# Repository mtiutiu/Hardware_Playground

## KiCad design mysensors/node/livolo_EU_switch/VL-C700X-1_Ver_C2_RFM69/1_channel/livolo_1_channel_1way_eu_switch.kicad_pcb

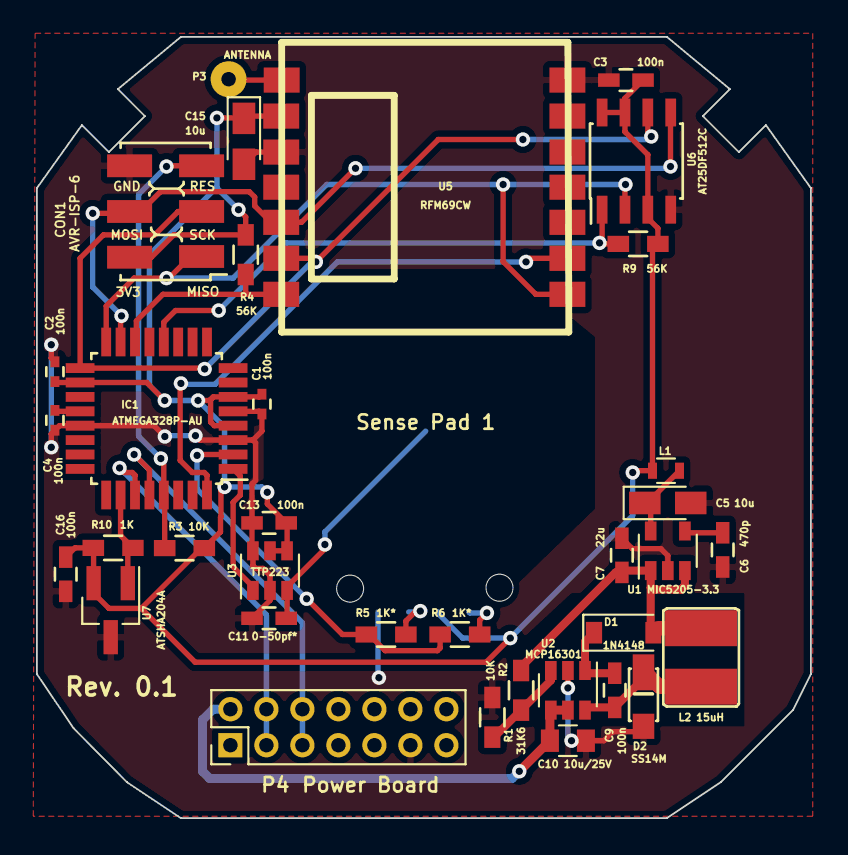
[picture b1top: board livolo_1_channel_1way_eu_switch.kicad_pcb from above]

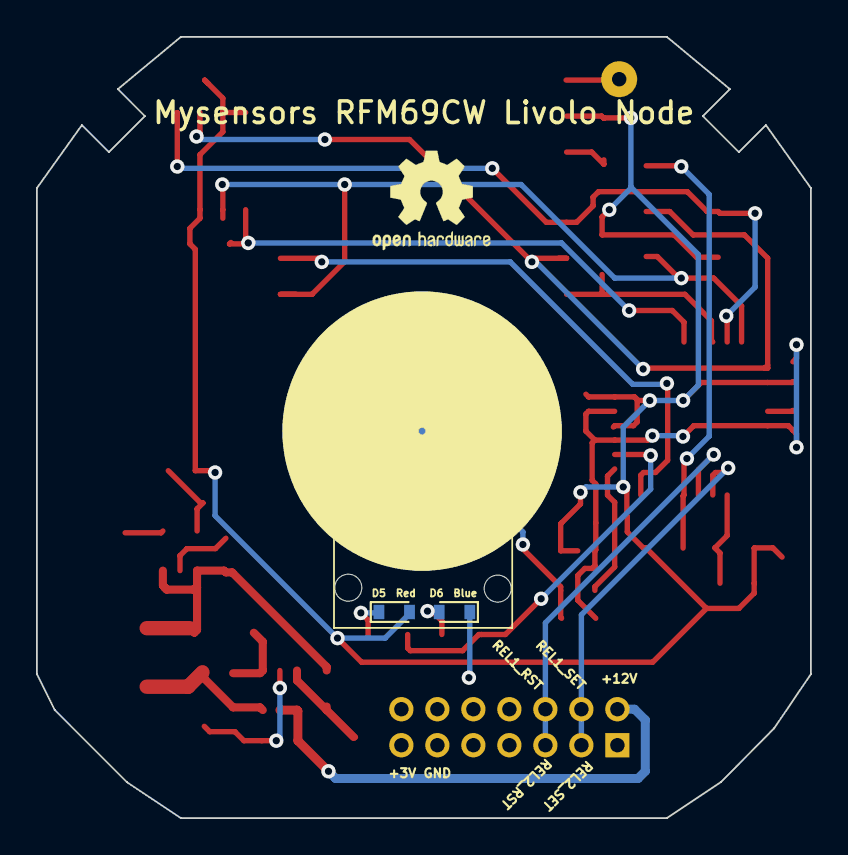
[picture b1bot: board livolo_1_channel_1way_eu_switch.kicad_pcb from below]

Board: 2 copper layers, 43.0 x 43.4 mm, 38 parts (2 on the bottom side), 26 nets.

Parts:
C1, C2, C4: 100n; C_0402
C3, C9, C13, C16: 100n; C_0603_HandSoldering
C5, C15: 10u; CP_Tantalum_Case-R_EIA-2012-12_Wave
C6: 470p; C_0603_HandSoldering
C7: 22u; C_0603_HandSoldering
C10: 10u/25V; C_0805
C11: 0-50pf*; C_0603_HandSoldering
CON1: AVR-ISP-6; AVR_ISP_SMT_Small_02x03
D1: 1N4148; SOD-123
D2: SS14M
D5: Red; D_0603
D6: Blue; D_0603
IC1: ATMEGA328P-AU; TQFP-32_7x7mm_Pitch0.8mm
L1: BLM18HE152SN1D; R_0603
L2: 15uH; VLCF4020T-150MR68
P1: Sense Pad 1; touch_pad_16mm
P3: ANTENNA; SolderWirePad_single_0-8mmDrill
P4: Power Board; Pin_Header_Straight_2x07_Pitch2.00mm
R1: 31K6; R_0603_HandSoldering
R2, R3: 10K; R_0603_HandSoldering
R4, R9: 56K; R_0603_HandSoldering
R5, R6: 1K*; R_0603_HandSoldering
R10: 1K; R_0603_HandSoldering
U1: MIC5205-3.3; SOT-23-5
U2: MCP16301; SOT-23-6
U3: TTP223; SOT-23-6
U5: RFM69CW
U6: AT25DF512C; SOIC-8_3.9x4.9mm_Pitch1.27mm
U7: ATSHA204A; SOT-23_Handsoldering

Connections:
+3V3: C1.1, C2.2, C3.2, C13.1, C15.1, C16.2, CON1.2, D5.2, IC1.4, IC1.6, IC1.18, L1.1, R3.1, R4.2, R9.1, R10.1, U3.4, U3.5, U5.2, U6.3, U6.7, U6.8, U7.2
/12Vcc: C10.1, P4.2, U2.4, U2.5
/ATSHA204A: IC1.26, R10.2, U7.1
/FLASH_SS: IC1.12, R9.2, U6.1
/INT: IC1.32, U5.9
/MISO: CON1.1, IC1.16, U5.8, U6.2
/MOSI: CON1.4, IC1.15, U5.5, U6.5
/RADIO_SS: IC1.14, R4.1, U5.7
/RESET: CON1.5, IC1.29, R3.2
/Relay1_Reset: IC1.28, P4.5, P4.6
/Relay1_Set: IC1.27, P4.3, P4.4
/S1_LEDs: IC1.2, R5.2, R6.2
/SCK: CON1.3, IC1.17, U5.6, U6.6
/TS1: IC1.1, U3.1
GND: C1.2, C2.1, C3.1, C4.1, C5.2, C6.2, C7.2, C10.2, C11.2, C13.2, C15.2, C16.1, CON1.6, D2.2, D6.1, IC1.3, IC1.5, IC1.21, P4.11, R2.1, U1.2, U2.2, U3.2, U3.6, U5.3, U5.14, U6.4, U7.3
unnamed: C4.2, IC1.20
unnamed: C5.1, L1.2, U1.5
unnamed: C6.1, U1.4
unnamed: C7.1, D1.2, L2.1, R1.2, U1.1, U1.3
unnamed: C9.1, D1.1, U2.1
unnamed: C9.2, D2.1, L2.2, U2.6
unnamed: C11.1, P1.1, U3.3
unnamed: D5.1, R6.1
unnamed: D6.2, R5.1
unnamed: P3.1, U5.1
unnamed: R1.1, R2.2, U2.3

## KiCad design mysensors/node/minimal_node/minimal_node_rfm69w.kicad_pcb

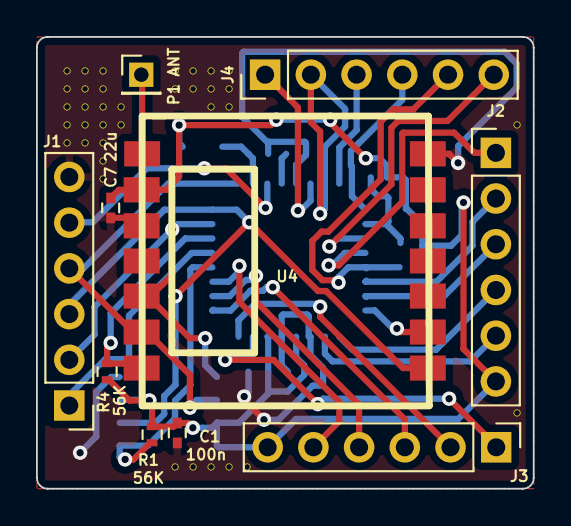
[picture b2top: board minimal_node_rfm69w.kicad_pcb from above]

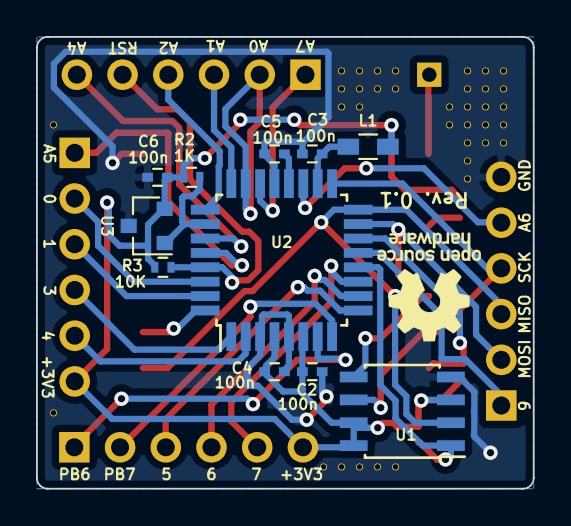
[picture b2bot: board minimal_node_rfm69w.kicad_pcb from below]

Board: 2 copper layers, 27.6 x 25.1 mm, 57 parts (11 on the bottom side), 30 nets.

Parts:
C1, C2, C3, C4, C5, C6: 100n; C_0402
C7: 22u; C_0402
J1, J2, J3, J4: CONN_01X06; Pin_Header_Straight_1x06_Pitch2.54mm
L1: BLM18HE152; R_0603_HandSoldering
P1: ANT; Pin_Header_Straight_1x01_Pitch2.00mm
R1, R4: 56K; R_0402
R2: 1K; R_0402
R3: 10K; R_0402
U1: AT25DF512C; SOIC-8_3.9x4.9mm_Pitch1.27mm
U2: ATMEGA328P-AU; TQFP-32_7x7mm_Pitch0.8mm
U3: ATSHA204A; SOT-23
U4: RFM69CW
V8_3, V8_4, V8_5, V8_6, V8_7, V9_3, V9_4, V9_5, V9_6, V9_7, V10_3, V10_4, V10_5, V10_6, V10_7, V10_8, V10_9, V11_5, V11_6, V14_3, V14_4, V14_25, V15_3, V15_4, V15_25, V16_3, V16_4, V16_5, V16_25, V17_3, V17_4, V17_5, V17_25, V18_25, V33_6, V33_22: AUTO_VIA; VIA_MATRIX

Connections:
+3V3: C1.2, C2.1, C4.2, C6.1, C7.1, J2.6, J3.6, L1.2, R1.2, R2.2, R3.1, R4.2, U1.3, U1.7, U1.8, U2.4, U2.6, U3.2, U4.2
/7: J3.1, U2.7
/8: J3.2, U2.8
/19: J1.5, U2.19
/22: J4.1, U2.22
/ATSHA204A: R2.1, U2.26, U3.1
/MISO: J1.3, U1.2, U2.16, U4.8
/MOSI: J1.2, U1.5, U2.15, U4.5
/RFM69W_INT: U2.32, U4.9
/RFM69W_SS: R4.1, U2.14, U4.7
/RST: J4.5, R3.2, U2.29
/SCK: J1.4, U1.6, U2.17, U4.6
/SPI_FLASH_SS: R1.1, U1.1, U2.12
GND: C1.1, C2.2, C3.1, C4.1, C5.1, C6.2, C7.2, J1.6, U1.4, U2.3, U2.5, U2.21, U3.3, U4.3, U4.14, V8_3.1, V8_4.1, V8_5.1, V8_6.1, V8_7.1, V9_3.1, V9_4.1, V9_5.1, V9_6.1, V9_7.1, V10_3.1, V10_4.1, V10_5.1, V10_6.1, V10_7.1, V10_8.1, V10_9.1, V11_5.1, V11_6.1, V14_3.1, V14_4.1, V14_25.1, V15_3.1, V15_4.1, V15_25.1, V16_3.1, V16_4.1, V16_5.1, V16_25.1, V17_3.1, V17_4.1, V17_5.1, V17_25.1, V18_25.1, V33_6.1, V33_22.1
unnamed: C3.2, L1.1, U2.18
unnamed: C5.2, U2.20
unnamed: J1.1, U2.13
unnamed: J2.1, U2.28
unnamed: J2.2, U2.30
unnamed: J2.3, U2.31
unnamed: J2.4, U2.1
unnamed: J2.5, U2.2
unnamed: J3.3, U2.9
unnamed: J3.4, U2.10
unnamed: J3.5, U2.11
unnamed: J4.2, U2.23
unnamed: J4.3, U2.24
unnamed: J4.4, U2.25
unnamed: J4.6, U2.27
unnamed: P1.1, U4.1

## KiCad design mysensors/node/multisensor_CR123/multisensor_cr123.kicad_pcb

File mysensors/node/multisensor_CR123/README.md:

## Mysensors RFM69W multisensor node(CR123)
More details here: https://www.openhardware.io/view/321/MySensors-RFM69W-multisensor-nodeCR123

##### 3D renderings of pcb

Top view | Bottom view
------------ | -------------
 | 

**Description:**

This is a Mysensors node using **RFM69W** radio module, **I2C based** temperature/humidity sensors(as external module) and **A3212** or equivalent hall effect sensors. 

**Key Features:**

 - **Si7021** temperature/humidity sensor(as a separate module bought from Aliexpress)
 - **A3212** hall efect sensor support
 - **DIP switch** for setting node ID statically
 - **MySensors** ready(**Atmega328p** + **RFM69W**)
 - **DC-DC boost** converter(**L6920** based) - can be bypassed if desired using the SMD jumpers on the board
 - **Small** board(**48 x 22mm**) using a **CR123** battery

**Work progress:**
 1. Test/verify the pcb board correctness(from both electrical and mechanical point of views) - **DONE**
 2. Produce the initial PCB's using some external PCB manufacturer - **DONE**
 3. Components assembly(soldering) - **DONE**
 4. Upload Mysensors temperature/humidity node sketch code - **DONE**
 5. Verify the real board with running code - **DONE**
 6. Code optimizations for low power operation - **DONE**
 7. Create project enclosure using a 3D printer - **DONE**

**Note:**

This module has been in production for about 2 months now and it's working stable. This is my first stable node created and I didn't provided any other features as signing support and SPI flash for OTA - so please bear this in mind. This is the final version of it and I won't invest any time/money or other resources to upgrade it. The project is open hardware anyway so anyone can do that if he/she wants.

**Credits:**
  
  All credits go to **MySensors** team for the great work and to the opensource community

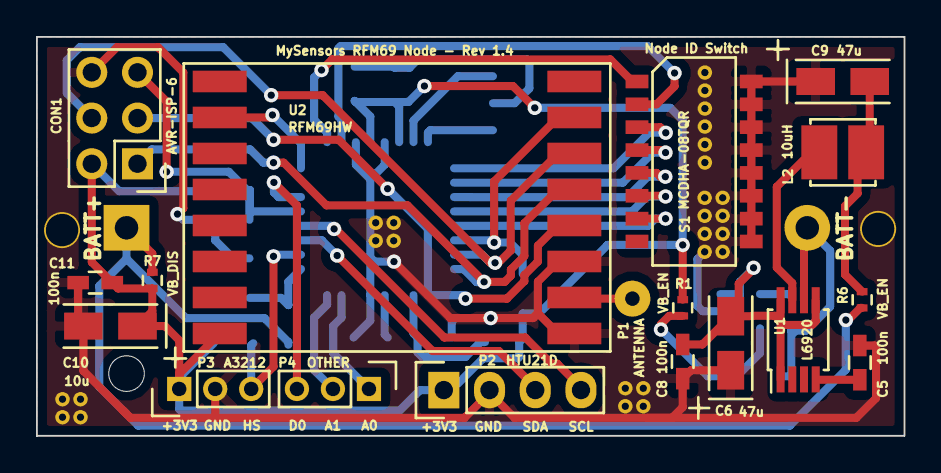
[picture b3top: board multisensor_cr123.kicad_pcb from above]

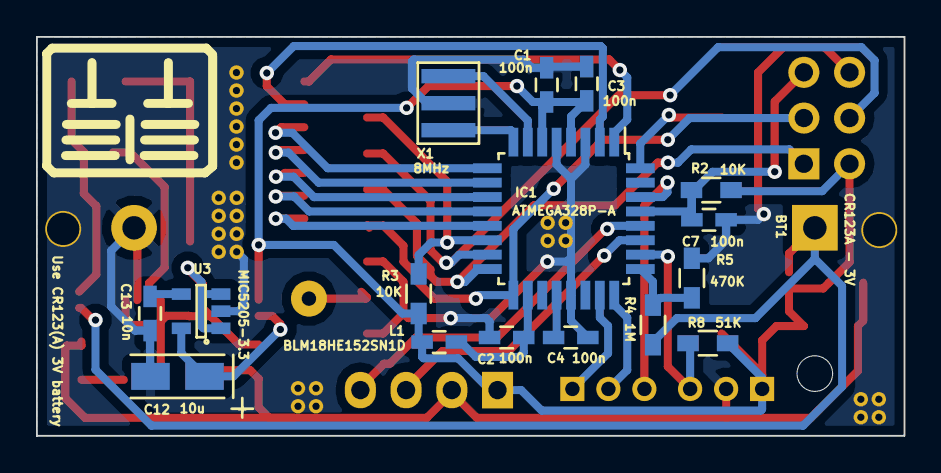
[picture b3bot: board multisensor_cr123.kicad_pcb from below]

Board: 2 copper layers, 48.2 x 22.2 mm, 35 parts (17 on the bottom side), 34 nets.

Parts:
BT1: CR123A - 3V; CR123_holder
C1, C2, C3, C4, C5, C7, C8, C11: 100n; C_0603_HandSoldering
C6, C9: 47u; TantalC_SizeA_EIA-3216_Wave
C10, C12: 10u; TantalC_SizeA_EIA-3216_Wave
C13: 10n; C_0603_HandSoldering
CON1: AVR-ISP-6; Pin_Header_Straight_2x03
IC1: ATMEGA328P-A; TQFP-32_7x7mm_Pitch0.8mm
L1: BLM18HE152SN1D; C_0603_HandSoldering
L2: 10uH; DLJ-3015
P1: ANTENNA; SolderWirePad_single_0-8mmDrill
P2: HTU21D; Pin_Header_Straight_1x04
P3: A3212; Pin_Header_Straight_1x03_Pitch2.00mm
P4: OTHER; Pin_Header_Straight_1x03_Pitch2.00mm
R1, R6: VB_EN; R_0402
R2, R3: 10K; R_0603_HandSoldering
R4: 1M; R_0603_HandSoldering
R5: 470K; R_0603_HandSoldering
R7: VB_DIS; R_0402
R8: 51K; R_0603_HandSoldering
S1: MCDHA-08TQR; DIPSWITCH_SMD_1.27-16
U1: L6920; MSOP-8_3x3mm_Pitch0.65mm
U2: RFM69HW; RFM69HW_SMD_Handsoldering
U3: MIC5205-3.3; SOT-23-5
X1: 8MHz; ZTTCR-3

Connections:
+3V3: C1.1, C3.2, C10.1, C11.1, CON1.2, IC1.4, IC1.6, L1.1, P2.1, P3.1, R1.2, R2.1, R3.2, R7.1, R8.1, U2.8
/A0: IC1.23, P4.1
/A1: IC1.24, P4.2
/C0: IC1.1, S1.1
/C1: IC1.2, S1.2
/C2: IC1.9, S1.3
/C3: IC1.10, S1.4
/C4: IC1.11, S1.5
/C5: IC1.12, S1.6
/C6: IC1.13, S1.7
/D0: IC1.30, P4.3
/HALL_SENSOR: IC1.26, P3.3, R8.2
/INT: IC1.32, U2.2
/MISO: CON1.1, IC1.16, U2.13
/MOSI: CON1.4, IC1.15, U2.14
/RESET: C7.2, CON1.5, IC1.29, R2.2
/SCK: CON1.3, IC1.17, U2.12
/SCL: IC1.28, P2.4
/SDA: IC1.27, P2.3
/SS: IC1.14, R3.1, U2.15
/V_BATT: IC1.25, R4.1, R5.2
/V_BOOST_IN: C9.2, L2.2, R6.2
GND: BT1.2, C1.2, C2.1, C3.1, C4.1, C5.2, C6.1, C7.1, C8.2, C9.1, C10.2, C11.2, C12.2, C13.2, CON1.6, IC1.3, IC1.5, IC1.21, P2.2, P3.2, R5.1, S1.9, S1.10, S1.11, S1.12, S1.13, S1.14, S1.15, S1.16, U1.6, U2.9, U2.11, U3.2, X1.3
unnamed: BT1.1, R4.2, R6.1, R7.2
unnamed: C2.2, IC1.18, L1.2
unnamed: C4.2, IC1.20
unnamed: C5.1, U1.4
unnamed: C6.2, C8.1, U1.1, U1.5, U1.8, U3.1, U3.3
unnamed: C12.1, R1.1, U3.5
unnamed: C13.1, U3.4
unnamed: IC1.7, X1.2
unnamed: IC1.8, X1.1
unnamed: L2.1, U1.7
unnamed: P1.1, U2.10

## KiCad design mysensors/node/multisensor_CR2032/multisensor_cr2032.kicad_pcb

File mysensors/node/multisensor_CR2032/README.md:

## Mysensors RFM69W multisensor node(CR2032)
More details here: https://www.openhardware.io/view/320/MySensors-RFM69W-multisensor-nodeCR2032

##### 3D renderings of pcb

Top view | Bottom view
------------ | -------------
 | 

**Description:**

This is a Mysensors node using **RFM69W** radio module, **Si7021** temperature/humidity sensor and **MAX44009** ambient light sensor. 

**Key Features:**

 - **Si7021** temperature/humidity sensor
 - **MAX44009** ambient light sensor
 - **ATSHA204A** for signing
 - **AT25DF512C-SSHN-B** SPI flash module for OTA
 - **MySensors** ready(**Atmega328p** + **RFM69W**)
 - **DC-DC boost** converter(**NCP1402** based) - can be bypassed using the on board jumpers
 - **Small** board(**36mm diameter**) using a **CR2032** coin cell

**Work progress:**
 1. Test/verify the pcb board correctness(from both electrical and mechanical point of views) - **TO DO**
 2. Produce the initial PCB's using some external PCB manufacturer
 3. Components assembly(soldering)
 4. Upload Mysensors temperature/humidity node sketch code
 5. Verify the real board with running code
 6. Code optimizations for low power operation
 7. Create project enclosure using a 3D printer

**Note: Work in progress(schematic/pcb will change).**

**HW Revisions:**
 - 0.1 - initial design
 - 0.2 - added option to bypass step-up converter using jumpers
 - 0.3 - added MAX44009 ambient light sensor
 - 0.4 - added A3212 hall sensor

**Kindly notice:**

The only thing I ask if using this project is to at least mention my name and if I don't ask too much you can also support my effort using the below button. Thanks for buying me a beer :).

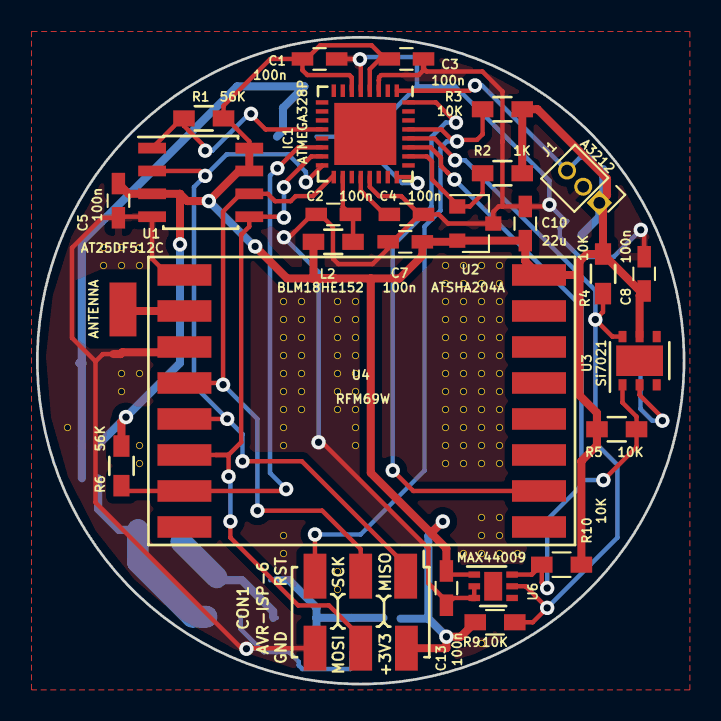
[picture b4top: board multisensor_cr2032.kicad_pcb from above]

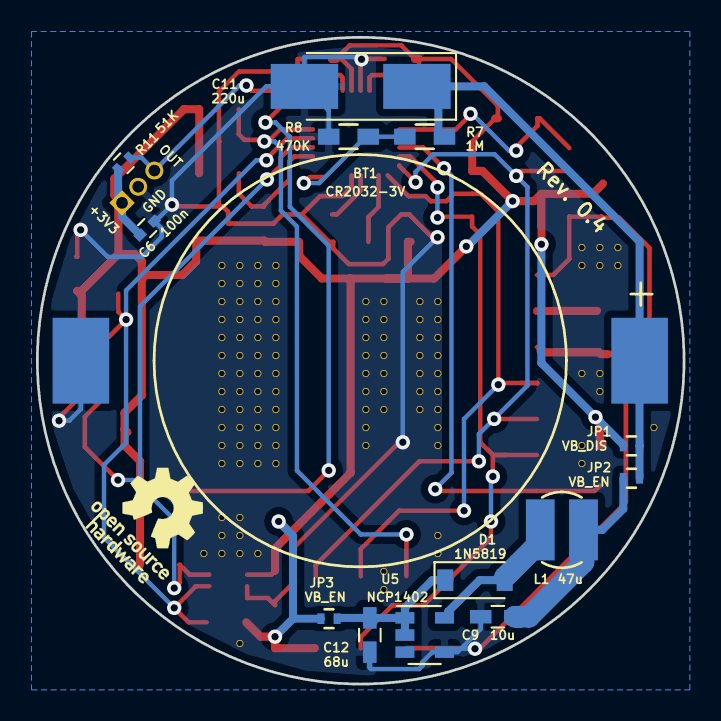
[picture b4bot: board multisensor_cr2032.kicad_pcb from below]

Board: 2 copper layers, 35.9 x 35.9 mm, 146 parts (14 on the bottom side), 21 nets.

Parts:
BT1: CR2032-3V; CR2032_BATT-HOLDER_SMT_H2
C1, C2, C3, C4, C5, C7, C8, C13: 100n; C_0603_HandSoldering
C6: 100n; C_0402
C9: 10u; C_0603_HandSoldering
C10: 22u; C_0603_HandSoldering
C11: 220u; CP_Tantalum_Case-C_EIA-6032-28_Hand
C12: 68u; C_0603_HandSoldering
CON1: AVR-ISP-6; AVR_ISP_SMT_Small_02x03
D1: 1N5819; D_SOD-123
IC1: ATMEGA328P; QFN-32-1EP_5x5mm_Pitch0.5mm
J1: A3212; Pin_Header_Straight_1x03_Pitch1.27mm
JP1, JP3: VB_EN; R_0402
JP2: VB_DIS; R_0402
L1: 47u; SDR0302
L2: BLM18HE152; R_0603_HandSoldering
P1: ANTENNA; 1pin_smd_2mm
R1, R6: 56K; R_0603_HandSoldering
R2: 1K; R_0603_HandSoldering
R3, R4, R5, R9, R10: 10K; R_0603_HandSoldering
R7: 1M; R_0603_HandSoldering
R8: 470K; R_0603_HandSoldering
R11: 51K; R_0402
U1: AT25DF512C; SOIC-8_3.9x4.9mm_Pitch1.27mm
U2: ATSHA204A; SOT-23
U3: Si7021; DFN-6-1EP_3x3mm_Pitch0.95mm
U4: RFM69W; RFM69HW_SMD_Handsoldering
U5: NCP1402; SOT-23-5
U6: MAX44009; DFN-6-1EP_2x2mm_Pitch0.65mm
V2_22, V4_12, V4_13, V5_12, V5_13, V5_19, V5_20, V6_12, V6_13, V6_19, V6_23, V6_24, V14_15, V14_16, V14_17, V14_18, V14_19, V14_20, V14_21, V14_22, V14_23, V14_28, V14_29, V15_15, V15_16, V15_17, V15_18, V15_19, V15_20, V15_21, V17_15, V17_16, V17_17, V17_18, V17_19, V17_20, V17_21, V17_30, V17_31, V18_15, V18_16, V18_17, V18_18, V18_19, V18_20, V18_21, V18_22, V18_23, V23_13, V23_14, V23_15, V23_16, V23_17, V23_18, V23_19, V23_20, V23_21, V23_22, V23_23, V23_24, V24_13, V24_14, V24_15, V24_16, V24_17, V24_18, V24_19, V24_20, V24_21, V24_22, V24_23, V24_24, V24_29, V25_13, V25_14, V25_15, V25_16, V25_17, V25_18, V25_19, V25_20, V25_21, V25_22, V25_23, V25_24, V25_27, V25_28, V25_29, V25_34, V26_13, V26_14, V26_15, V26_16, V26_17, V26_18, V26_19, V26_20, V26_21, V26_22, V26_23, V26_24, V26_27, V26_28, V26_29, V27_29: AUTO_VIA; VIA_MATRIX

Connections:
+3V3: C1.1, C3.2, C5.2, C6.2, C7.1, C8.1, C10.1, C13.1, CON1.2, IC1.4, IC1.6, J1.1, JP2.2, JP3.2, L2.2, R1.2, R2.2, R3.1, R4.2, R5.2, R6.2, R9.2, R10.2, R11.1, U1.3, U1.7, U1.8, U2.2, U3.5, U4.8, U6.1
/A3212: IC1.1, J1.3, R11.2
/ATSHA204A: IC1.26, R2.1, U2.1
/MISO: CON1.1, IC1.16, U1.2, U4.13
/MOSI: CON1.4, IC1.15, U1.5, U4.14
/RFM69W_INT: IC1.32, U4.2
/RFM69W_SS: IC1.14, R6.1, U4.15
/RST: CON1.5, IC1.29, R3.2
/SCK: CON1.3, IC1.17, U1.6, U4.12
/SCL: IC1.28, R4.1, R9.1, U3.6, U6.5
/SDA: IC1.27, R5.1, R10.1, U3.1, U6.6
/SPI_FLASH_SS: IC1.12, R1.1, U1.1
/VB_IN: C9.2, JP1.1, L1.1
/V_BATT_MON: IC1.24, R7.1, R8.2
GND: BT1.2, C1.2, C2.1, C3.1, C4.1, C5.1, C6.1, C7.2, C8.2, C9.1, C10.2, C11.2, C12.1, C13.2, CON1.6, IC1.3, IC1.5, IC1.21, J1.2, R8.1, U1.4, U2.3, U3.2, U4.9, U4.11, U5.4, U6.2, U6.3, V2_22.1, V4_12.1, V4_13.1, V5_12.1, V5_13.1, V5_19.1, V5_20.1, V6_12.1, V6_13.1, V6_19.1, V6_23.1, V6_24.1, V14_15.1, V14_16.1, V14_17.1, V14_18.1, V14_19.1, V14_20.1, V14_21.1, V14_22.1, V14_23.1, V14_28.1, V14_29.1, V15_15.1, V15_16.1, V15_17.1, V15_18.1, V15_19.1, V15_20.1, V15_21.1, V17_15.1, V17_16.1, V17_17.1, V17_18.1, V17_19.1, V17_20.1, V17_21.1, V17_30.1, V17_31.1, V18_15.1, V18_16.1, V18_17.1, V18_18.1, V18_19.1, V18_20.1, V18_21.1, V18_22.1, V18_23.1, V23_13.1, V23_14.1, V23_15.1, V23_16.1, V23_17.1, V23_18.1, V23_19.1, V23_20.1, V23_21.1, V23_22.1, V23_23.1, V23_24.1, V24_13.1, V24_14.1, V24_15.1, V24_16.1, V24_17.1, V24_18.1, V24_19.1, V24_20.1, V24_21.1, V24_22.1, V24_23.1, V24_24.1, V24_29.1, V25_13.1, V25_14.1, V25_15.1, V25_16.1, V25_17.1, V25_18.1, V25_19.1, V25_20.1, V25_21.1, V25_22.1, V25_23.1, V25_24.1, V25_27.1, V25_28.1, V25_29.1, V25_34.1, V26_13.1, V26_14.1, V26_15.1, V26_16.1, V26_17.1, V26_18.1, V26_19.1, V26_20.1, V26_21.1, V26_22.1, V26_23.1, V26_24.1, V26_27.1, V26_28.1, V26_29.1, V27_29.1
unnamed: BT1.1, C11.1, JP1.2, JP2.1, R7.2
unnamed: C2.2, IC1.18, L2.1
unnamed: C4.2, IC1.20
unnamed: C12.2, D1.1, JP3.1, U5.1, U5.2
unnamed: D1.2, L1.2, U5.5
unnamed: P1.1, U4.10

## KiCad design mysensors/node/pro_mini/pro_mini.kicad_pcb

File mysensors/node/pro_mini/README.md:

## Mysensors NRF24L01 simple node with voltage booster

##### 3D renderings of pcb

Top view | Bottom view
------------ | -------------
 | 

**Kindly notice:**

The only thing I ask if using this project is to at least mention my name and if I don't ask too much you can also support my effort using the below button. Thanks for buying me a beer :).

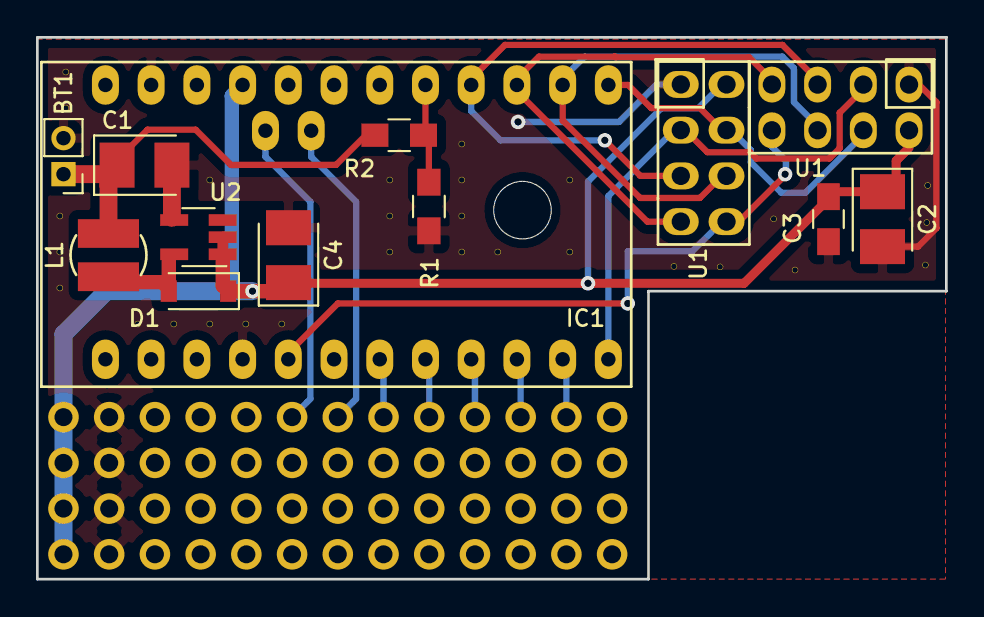
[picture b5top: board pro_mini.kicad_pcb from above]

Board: 2 copper layers, 50.5 x 30.1 mm, 41 parts (0 on the bottom side), 11 nets.

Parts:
BT1: 3V; Pin_Header_Straight_1x02_Pitch2.00mm
C1: 10u; CP_Tantalum_Case-B_EIA-3528-21_Reflow
C2: 22u; CP_Tantalum_Case-B_EIA-3528-21_Reflow
C3: 100n; C_0805_HandSoldering
C4: 68u; CP_Tantalum_Case-B_EIA-3528-21_Reflow
D1: 1N5819; D_SOD-123
IC1: ArduinoProMini; pro_mini
L1: 47u; SDR0302
R1: 10K; R_0805_HandSoldering
R2: 22K; R_0805_HandSoldering
U1, U1#2: NRF24L01
U2: NCP1402; SOT-23-5_HandSoldering
V7_1, V7_2, V7_5, V7_6, V7_7, V9_8, V10_8, V11_4, V11_8, V12_8, V13_8, V16_4, V16_5, V16_6, V18_3, V18_4, V18_5, V18_6, V18_6#2, V18_6#3, V18_6#4, V18_6#5, V18_6#6, V18_6#7, V18_6#8, V19_6, V21_4, V21_6: AUTO_VIA; VIA_MATRIX

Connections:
+3.3V: C2.1, C3.1, C4.1, D1.1, IC1.21, U1.2, U1#2.2, U2.1, U2.2
/RF_CE: IC1.12, U1.3, U1#2.3
/RF_CSN: IC1.13, U1.4, U1#2.4
/RF_IRQ: IC1.5, U1.8, U1#2.8
/RF_MISO: IC1.15, U1.7, U1#2.7
/RF_MOSI: IC1.14, U1.6, U1#2.6
/RF_SCK: IC1.16, U1.5, U1#2.5
/V_BATT: IC1.17, R1.2, R2.2
GND: BT1.2, C1.2, C2.2, C3.2, C4.2, IC1.4, IC1.23, R1.1, U1.1, U1#2.1, U2.4, V7_1.1, V7_2.1, V7_5.1, V7_6.1, V7_7.1, V9_8.1, V10_8.1, V11_4.1, V11_8.1, V12_8.1, V13_8.1, V16_4.1, V16_5.1, V16_6.1, V18_3.1, V18_4.1, V18_5.1, V18_6.1, V18_6#2.1, V18_6#3.1, V18_6#4.1, V18_6#5.1, V18_6#6.1, V18_6#7.1, V18_6#8.1, V19_6.1, V21_4.1, V21_6.1
unnamed: BT1.1, C1.1, L1.1, R2.1
unnamed: D1.2, L1.2, U2.5

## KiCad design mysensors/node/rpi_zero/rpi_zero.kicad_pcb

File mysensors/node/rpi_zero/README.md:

## Raspberry Pi Zero(W) Shield(HAT)

##### 3D renderings of pcb

Top view | Bottom view
------------ | -------------
 | 

**Description:**

This is a shield(or HAT) for the Raspberry Pi Zero(W) Linux SBC

**Key Features:**

 - **DS18B20** temperature/humidity sensor
 - **RFM69W** radio module
 - **OLED Display(SSD1306 - 128x32)**
 - **LED Bargraph**
 - **SMD Switches**

**Work progress:**
 1. Test/verify the pcb board correctness(from both electrical and mechanical point of views) - **DONE**
 2. Produce the initial PCB's using some external PCB manufacturer - **IN PROGRESS**
 3. Components assembly(soldering)
 4. Verify the real board with running code
 5. Create project enclosure using a 3D printer

**Note: Work in progress(schematic/pcb will change).**

**HW Revisions:**
 - 0.1 - initial design

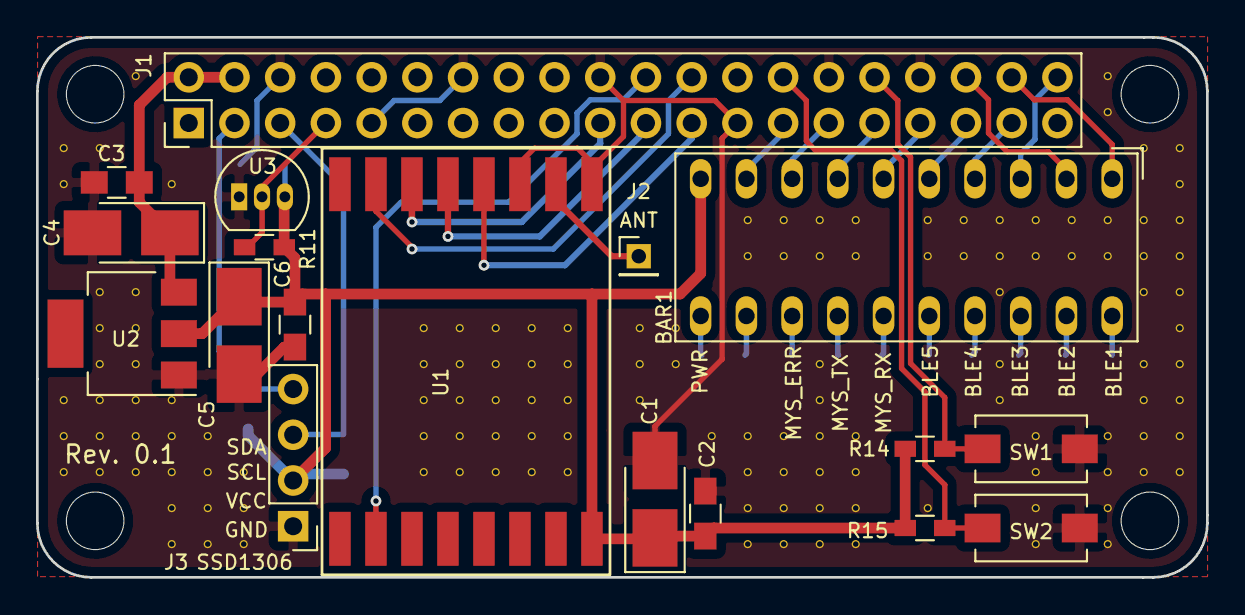
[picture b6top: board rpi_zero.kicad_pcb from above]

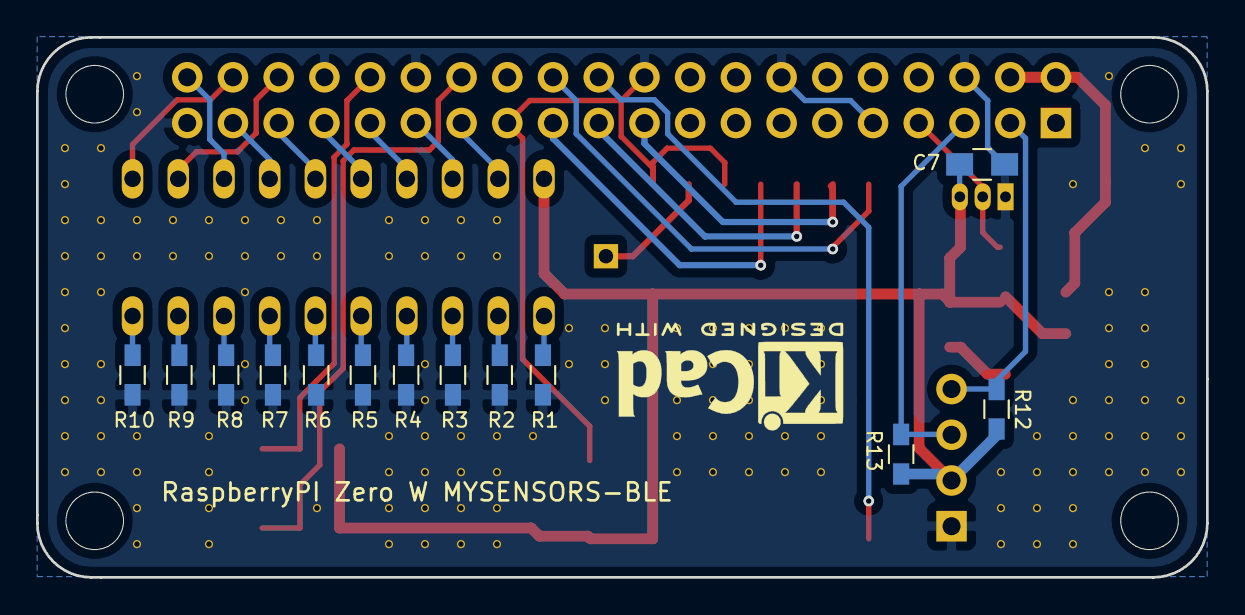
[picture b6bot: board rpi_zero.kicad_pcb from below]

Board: 2 copper layers, 65.0 x 30.0 mm, 164 parts (13 on the bottom side), 33 nets.

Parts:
BAR1: HDSP-4850_2; HDSP-4850
C1, C4, C5: 22u; CP_Tantalum_Case-B_EIA-3528-21_Hand
C2, C3, C6, C7: 100n; C_0805_HandSoldering
J1: RPI_Zero_W; Pin_Header_Straight_2x20_Pitch2.54mm
J2: ANT; Pin_Header_Straight_1x01_Pitch2.00mm
J3: SSD1306; Pin_Header_Straight_1x04_Pitch2.54mm
R1, R2, R3, R4, R5, R6, R7, R8, R9, R10: 220; R_0603_HandSoldering
R11, R12, R13: 4K7; R_0603_HandSoldering
R14, R15: 10K; R_0603_HandSoldering
SW1, SW2: BLE; SW_SPST_EVQPE1
U1: RFM69HW; RFM69HW_SMD_Handsoldering
U2: AMS1117; SOT-223
U3: DS18B20; TO-92_Inline_Narrow_Oval
V3_4, V3_5, V3_11, V3_12, V3_13, V4_4, V4_8, V4_9, V4_10, V4_11, V4_12, V4_13, V5_2, V5_8, V5_9, V5_10, V5_11, V5_12, V5_13, V6_5, V6_11, V6_12, V6_13, V6_14, V6_15, V7_12, V7_13, V7_14, V7_15, V8_13, V8_14, V8_15, V13_9, V13_10, V13_11, V13_12, V13_13, V14_9, V14_10, V14_11, V14_12, V14_13, V15_9, V15_10, V15_11, V15_12, V15_13, V16_9, V16_10, V16_11, V16_12, V16_13, V17_9, V17_10, V17_11, V17_12, V17_13, V19_9, V19_10, V19_11, V20_9, V20_10, V21_12, V22_6, V22_7, V22_12, V22_13, V22_14, V22_15, V23_6, V23_7, V23_12, V23_13, V23_14, V23_15, V24_6, V24_7, V24_10, V24_11, V24_12, V24_13, V24_14, V24_15, V25_6, V25_7, V25_12, V25_13, V25_14, V25_15, V27_6, V27_7, V27_14, V28_6, V28_7, V29_6, V29_7, V29_8, V29_10, V29_11, V30_6, V30_7, V30_12, V30_13, V30_14, V30_15, V31_6, V31_7, V32_2, V32_3, V32_6, V32_7, V32_12, V32_13, V32_14, V32_15, V33_4, V33_6, V33_7, V33_8, V33_10, V33_11, V33_12, V33_13, V34_4, V34_5, V34_6, V34_7, V34_8, V34_9, V34_10, V34_11, V34_12, V34_13: AUTO_VIA; VIA_MATRIX

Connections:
+3V3: BAR1.10, C1.1, C2.2, C5.1, C6.2, C7.1, J3.2, R11.1, R12.2, R13.2, R14.1, R15.1, U1.8, U2.2, U3.3
+5V: C3.2, C4.1, J1.2, J1.4, U2.3
/RFM69_CE: J1.22, U1.2
/RFM69_CS: J1.24, U1.15
/RFM69_MISO: J1.21, U1.13
/RFM69_MOSI: J1.19, U1.14
/RFM69_SCK: J1.23, U1.12
/SSD_SCL: J1.5, J3.3, R13.1
/SSD_SDA: J1.3, J3.4, R12.1
/SW1: J1.32, R14.2, SW1.1
/SW2: J1.28, R15.2, SW2.1
GND: C1.2, C2.1, C3.1, C4.2, C5.2, C6.1, C7.2, J1.6, J1.9, J1.14, J1.20, J1.25, J1.30, J1.34, J1.39, J3.1, R1.2, R2.2, R3.2, R4.2, R5.2, R6.2, R7.2, R8.2, R9.2, R10.2, SW1.2, SW2.2, U1.9, U1.11, U2.1, U3.1, V3_4.1, V3_5.1, V3_11.1, V3_12.1, V3_13.1, V4_4.1, V4_8.1, V4_9.1, V4_10.1, V4_11.1, V4_12.1, V4_13.1, V5_2.1, V5_8.1, V5_9.1, V5_10.1, V5_11.1, V5_12.1, V5_13.1, V6_5.1, V6_11.1, V6_12.1, V6_13.1, V6_14.1, V6_15.1, V7_12.1, V7_13.1, V7_14.1, V7_15.1, V8_13.1, V8_14.1, V8_15.1, V13_9.1, V13_10.1, V13_11.1, V13_12.1, V13_13.1, V14_9.1, V14_10.1, V14_11.1, V14_12.1, V14_13.1, V15_9.1, V15_10.1, V15_11.1, V15_12.1, V15_13.1, V16_9.1, V16_10.1, V16_11.1, V16_12.1, V16_13.1, V17_9.1, V17_10.1, V17_11.1, V17_12.1, V17_13.1, V19_9.1, V19_10.1, V19_11.1, V20_9.1, V20_10.1, V21_12.1, V22_6.1, V22_7.1, V22_12.1, V22_13.1, V22_14.1, V22_15.1, V23_6.1, V23_7.1, V23_12.1, V23_13.1, V23_14.1, V23_15.1, V24_6.1, V24_7.1, V24_10.1, V24_11.1, V24_12.1, V24_13.1, V24_14.1, V24_15.1, V25_6.1, V25_7.1, V25_12.1, V25_13.1, V25_14.1, V25_15.1, V27_6.1, V27_7.1, V27_14.1, V28_6.1, V28_7.1, V29_6.1, V29_7.1, V29_8.1, V29_10.1, V29_11.1, V30_6.1, V30_7.1, V30_12.1, V30_13.1, V30_14.1, V30_15.1, V31_6.1, V31_7.1, V32_2.1, V32_3.1, V32_6.1, V32_7.1, V32_12.1, V32_13.1, V32_14.1, V32_15.1, V33_4.1, V33_6.1, V33_7.1, V33_8.1, V33_10.1, V33_11.1, V33_12.1, V33_13.1, V34_4.1, V34_5.1, V34_6.1, V34_7.1, V34_8.1, V34_9.1, V34_10.1, V34_11.1, V34_12.1, V34_13.1
unnamed: BAR1.1, J1.38
unnamed: BAR1.2, J1.36
unnamed: BAR1.3, J1.40
unnamed: BAR1.4, J1.37
unnamed: BAR1.5, J1.35
unnamed: BAR1.6, J1.33
unnamed: BAR1.7, J1.31
unnamed: BAR1.8, J1.29
unnamed: BAR1.9, J1.27
unnamed: BAR1.11, R1.1
unnamed: BAR1.12, R2.1
unnamed: BAR1.13, R3.1
unnamed: BAR1.14, R4.1
unnamed: BAR1.15, R5.1
unnamed: BAR1.16, R6.1
unnamed: BAR1.17, R7.1
unnamed: BAR1.18, R8.1
unnamed: BAR1.19, R9.1
unnamed: BAR1.20, R10.1
unnamed: J1.7, R11.2, U3.2
unnamed: J2.1, U1.10
